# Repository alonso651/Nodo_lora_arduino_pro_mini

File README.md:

Nodo loRaWan para Arduino Pro Mini Atmega328p 3.3v
==================================================
Febrero de 2019 

Este programa fue desarrollado a partir del código ejemplo de la libreria LMiC 1.51 port to ESP8266 and Arduino [LMiC-v1.51](libraries/lmic-v1.51/README.md), 
publicada en http://things4u.github.io por M. Westenberg.

Esta libreria implementa la pila para una red LoRa.
Contiene la pila completa de LoRa y funciona en la plataforma Teensy, ESP8266 y en el Ardino Atmega328.

LMIC 1.5 port to ESP8266 and Arduino esta compuesta de dos bibliotecas existentes:

1. La biblioteca LMIC-1.5 de IBM, que fue portada a Arduino IDE por Thomas Telkamp y Matthijs Kooijman
2. La pequeña implementación para Arduino hecha por Gerben den Hartog para Ideetron.

Nodo LoRaWAN
------------
Este programa envia un paquete LoRaWAN válido con la lectura de sensores al servidor The Things Network (TTN).

Utiliza el método de autenticación ABP, tambien es posible utilizar el método de activación OTAA, 
aunque este no fue probado aún.

Se utilizó la Banda de frecuencias ISM US915 MHz, que cuenta con 72 canales, 
de los cuales solo utilizamos los 8 canales de la segunda sub banda (Sub Banda 1).

Sub banda 1 (903.9 - 905.3 MHz): 

	· Canal 0 - 903.9 MHz
	· Canal 1 - 904.1 MHz
	· Canal 2 - 904.3 MHz
	· Canal 3 - 904.5 MHz
	· Canal 4 - 904.7 MHz
	· Canal 5 - 904.9 MHz
	· Canal 6 - 905.1 MHz
	· Canal 7 - 905.3 MHz
Es posible utilizar los factores de esparcimiento SF (Spreading Factor) del 7 al 12, solo fue probado 
con el SF7.

Hardware
--------
	· Arduino Pro Mini Atmega328p 3,3V 8MHz
	· HopeRF RFM95w de 915MHz  

Conexiones
----------
	 _____________________________
	|   RFM95w   |Arduino Pro Mini|
	|____________|________________|
	|GND         |GND             |
	|3.3v        |VCC (3.3v)      |
	|MISO        |12              |
	|MOSI        |11              |
	|SCK         |13              |
	|NSS         |10              |
	|DIO0        |4               |
	|DIO1        |5               |
	|DIO2        |7               |
	|____________|________________|

Modificaciónes hechas a la libreria LMIC 1.5 port to ESP8266 and Arduino:
-------------------------------------------------------------------------
lmic.cpp: LMIC_disableChannel(u1_t channel) 

	//LMIC.channelMap[channel/4] &= ~(1<<(channel&0xF)); 
    LMIC.channelMap[channel/16] &= ~(1<<(channel&0xF));

TTGO Pro Mini_LORA 20180926 - T-DEER:
-------------------------------------

	· Es necesario conectar dos pines de la placa entre si (puente) D5 - IO1
	· La definicion de pines es diferente que en el Arduino Pro Mini (Descomentar en el código fuente 
	y comentar la definición de pines anterior)
	· Se lo programa como Arduino UNO (En Arduino IDE)

	.

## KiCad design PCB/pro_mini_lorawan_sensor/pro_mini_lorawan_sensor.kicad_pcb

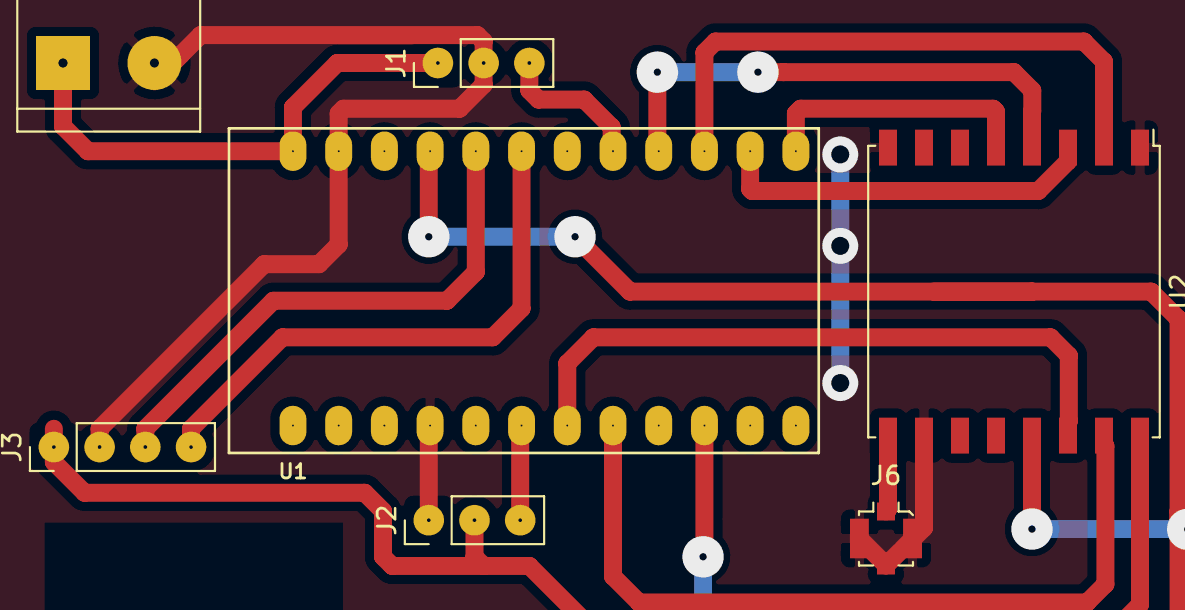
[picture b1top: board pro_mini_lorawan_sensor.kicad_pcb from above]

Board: 2 copper layers, 7 parts (0 on the bottom side), 15 nets.

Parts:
J1: Sensor de Humo; PinHeader_1x03_P2.54mm_Vertical
J2: Sensor de Llama; PinHeader_1x03_P2.54mm_Vertical
J3: BME280; PinHeader_1x04_P2.54mm_Vertical
J4: Entrada 5V; TerminalBlock_bornier-2_P5.08mm
J6: Conector Antena; U.FL_Molex_MCRF_73412-0110_Vertical
U1: pro_mini
U2: RFM95W; HOPERF_RFM9XW_SMD

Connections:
/3v3: J2.2, J3.1, U1.21, U2.13
/5V: J1.1, J4.1, U1.24
/A0: J1.3, U1.17
/ANT: J6.1, U2.9
/D3: J2.3, U1.6
/DIO0: U1.7, U2.14
/DIO1: U1.8, U2.15
/DIO2: U1.10, U2.16
/GND: J1.2, J2.1, J3.2, J4.2, J6.2, U1.4, U1.23, U2.1, U2.8, U2.10
/MISO: U1.15, U2.2
/MOSI: U1.14, U2.3
/NSS: U1.13, U2.5
/SCK: U1.16, U2.4
/SCL: J3.4, U1.19
/SDA: J3.3, U1.20

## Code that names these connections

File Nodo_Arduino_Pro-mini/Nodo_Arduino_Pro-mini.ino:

/*Nodo LoRa ABP Arduino Pro Mini 3v3 Atmega328p 8MHz

  Banda de frecuencia US915 MHz
  Sub Banda 1 (903.9 - 905.3) ---> Configuración del Gateway Single Channel ESP
  Canal 0 (de la sub banda 1) ---> Configuración del Gateway Single Channel ESP
  Canal en el que envia 903.9 MHz (canal 8 de 72)

  Radio HopeRF RFM95w (SX1276) 915MHz 

  Libreria: LMiC v1.5 *Modificada*
    Modificación: lmic.cpp LMIC_disableChannel(u1_t channel) 
      //LMIC.channelMap[channel/4] &= ~(1<<(channel&0xF)); 
      LMIC.channelMap[channel/16] &= ~(1<<(channel&0xF));

  Conexión de pines (Arduino Pro Mini):
   _____________________________
  |   RFM95w   |Arduino Pro Mini|
  |____________|________________|
  |GND         |GND             |
  |3.3v        |VCC (3.3v)      |
  |MISO        |12              |
  |MOSI        |11              |
  |SCK         |13              |
  |NSS         |10              |
  |DIO0        |4               |
  |DIO1        |5               |
  |DIO2        |7               |
  |____________|________________|

  Conexión de pines (TTGO Pro Mini_LORA - T-DEER):

    Puente entre los pines D5 y IO1 (Necesario para que envie mas de un paquete)
*/


//#define WAIT_SECS 120   //60 Segundos en Arduino Pro Mini
//#define WAIT_SECS 60  //60 Segundos en TTGO Pro Mini_LORA - T-DEER
#define WAIT_SECS 15  //15 Segundos en TTGO Pro Mini_LORA - T-DEER


#if defined(__AVR__)
#include <avr/pgmspace.h>
#include <Arduino.h>
#elif defined(ARDUINO_ARCH_ESP8266)
#include <ESP.h>
#elif defined(__MKL26Z64__)
#include <Arduino.h>
#else
#error Unknown architecture in aes.cpp
#endif

#include "lmic.h"
#include "hal/hal.h"
#include <SPI.h>

//---------------------------------------------------------
// Declaracion de variables
//---------------------------------------------------------

// Contador de tramas
int count=0;

// LoRaWAN Application identifier (AppEUI)
// No usado
static const u1_t APPEUI[8] PROGMEM = { 0x02, 0x00, 0x00, 0x00, 0x00, 0xEE, 0xFF, 0xC0 };

// LoRaWAN DevEUI
// No usado
static const u1_t DEVEUI[8] PROGMEM  = { 0x42, 0x42, 0x45, 0x67, 0x89, 0xAB, 0xCD, 0xEF };

// LoRaWAN NwkSKey, Network Session Key 
// Network Session Key The Things Network
unsigned char NwkSkey[16] =     { 0xE9, 0x01, 0xE2, 0x79, 0x10, 0x18, 0xF1, 0x40, 0xB7, 0xF7, 0xBA, 0x6D, 0x5C, 0x04, 0x01, 0xB7 };

// LoRaWAN AppSKey, Application Session Key
// Application Session Key para desencriptación de mensajes en The Things Network
unsigned char AppSkey[16] =   { 0x0E, 0xBE, 0x00, 0xE7, 0x66, 0x10, 0xE5, 0x3A, 0x19, 0x0B, 0xC6, 0x8C, 0x71, 0x1C, 0xAA, 0x22 };


#define msbf4_read(p)   (u4_t)((u4_t)(p)[0]<<24 | (u4_t)(p)[1]<<16 | (p)[2]<<8 | (p)[3])

// LoRaWAN end-device address (DevAddr)
unsigned char DevAddr[4] = { 0x26, 0x06, 0x2C, 0xE1 };


// ----------------------------------------------------------------------------
// APPLICATION CALLBACKS
// ----------------------------------------------------------------------------

// Desabilitar todos los canales, excepto el canal definido en el if de ForceTxSingleChannelDr()
// Setear el SF en LMIC_setDrTxpow() al final de esta función.
// Esto solo afecta a los mensajes enviados (uplinks). 

void forceTxSingleChannelDr() {
    for(int j=0; j<71; j++) { // US i<71 canales
        if(j != 8) {
            LMIC_disableChannel(j);
        }
    }
    // Set data rate (SF) and transmit power for uplink
    LMIC_setDrTxpow(DR_SF10, 14);
}

// provide application router ID (8 bytes, LSBF)
void os_getArtEui (u1_t* buf) {
    memcpy(buf, APPEUI, 8);
}

// provide device ID (8 bytes, LSBF)
void os_getDevEui (u1_t* buf) {
    memcpy(buf, DEVEUI, 8);
}

// provide device key (16 bytes)
void os_getDevKey (u1_t* buf) {
    memcpy(buf, NwkSkey, 16);
}

int debug=1;
uint8_t mydata[64];
static osjob_t sendjob;

// ----------------------------------------------------------------------------
// Pin mapping (Arduino Pro Mini)
// ----------------------------------------------------------------------------

// lmic_pinmap pins = {
//   .nss = 10,          // Conectado a D10 (Arduino Pro Mini)
//   .rxtx = 0,          // No conectar al RFM92/RFM95
//   .rst = 0,           // No conectar al RFM92/RFM95
//   .dio = {4, 5, 7},   // Especificación de pines DIO0, DIO1, DIO2 (RFM95)
//                       // Conectado a D4, D5, D7 (Arduino Pro Mini)
// };

// ----------------------------------------------------------------------------
// Pin mapping (TTGO Pro Mini_LORA 20180926 - T-DEER) 
// ----------------------------------------------------------------------------

lmic_pinmap pins = {
  .nss = 10,          // Conectado a D10 (TTGO Pro Mini_LORA)
  .rxtx = 0,          // No conectar al RFM92/RFM95
  .rst = 9,           // Conectado a D9 (TTGO Pro Mini_LORA)
  .dio = {2, 5, 0},   // Especificación de pines DIO0, DIO1, DIO2 (RFM95)
                      // Conectado a D2, D5, No Conectar (TTGO Pro Mini_LORA)
};

// ----------------------------------------------------------------------------
// Declaración de funciones
// ----------------------------------------------------------------------------

void onEvent (ev_t ev) {

    switch(ev) {
      // scheduled data sent (optionally data received)
      // note: this includes the receive window!
      case EV_TXCOMPLETE:
          // use this event to keep track of actual transmissions
          Serial.print("EV_TXCOMPLETE, tiempo: ");
          //Serial.print((millis() / 1000)/2); //Pro Mini
          Serial.print((millis() / 1000));
          Serial.println(" Segundos");
          if(LMIC.dataLen) { // Datos recibidos en la ventana de recepción (RX slot) luego del envio de datos (TX)
              Serial.println("Data Received");
          }
          break;
       default:
          break;
    }
}

void do_send(osjob_t* j){
    delay(1);                         // delay agregado para la comunicación serial
      Serial.print("Tiempo: ");
      //Serial.print((millis() / 1000)/2); //Pro Mini
      Serial.print((millis() / 1000));
      Serial.println(" Segundos");
      // Muestra el canal TX 
      Serial.print("Enviado. Canal: ");
      Serial.println(LMIC.txChnl);
      Serial.print("Opmode check: ");
      // Check if there is not a current TX/RX job running
    if (LMIC.opmode & (1 << 7)) {
      Serial.println("OP_TXRXPEND, not sending");
    } 
  else {
  
    strcpy((char *) mydata,"Arduino Pro Mini"); //Mensaje que se envia a TTN
    LMIC_setTxData2(1, mydata, strlen((char *)mydata), 0);
    }
    // Schedule a timed job to run at the given timestamp (absolute system time)
    os_setTimedCallback(j, os_getTime()+sec2osticks(WAIT_SECS), do_send);
         
}

// ----------------------------------------------------------------------------
// SETUP
// ----------------------------------------------------------------------------
void setup() {
  Serial.begin(115200);

  // Inicializacion de LMiC
  os_init();
  // Definición de la banda de frecuencia a utilizar (No se si cumple alguna función esto aquí)
  #if defined(CFG_us915)
  LMIC.freq = 903900000;
  #endif
  // Resetea el estado de la MAC. Sesión o datos pendientes de envio serán descartados
  LMIC_reset();
  // Establece la sesión con los parametros suministrados en la sección "Declaración de Variables"
  LMIC_setSession (0x1, msbf4_read(DevAddr), (uint8_t*)NwkSkey, (uint8_t*)AppSkey);
  // Desabilita la adaptación de SF (configuración para nodos móviles)
  LMIC_setAdrMode(0);
  // Disabilita link check validation
  LMIC_setLinkCheckMode(0);
  // Desabilita beacon tracking
  LMIC_disableTracking ();
  // Desabilita la recepcion periodica de datos (configuración para dispositivos LoRaWAN Clase A)
  LMIC_stopPingable();
  // Establece el canal, SF y potencia del transmisor para el envio de datos
  forceTxSingleChannelDr(); //reemplazar valores en la definición de la función forceTxSingleChannelDr() en la sección "Declaración de funciones"
  
#if defined(__AVR__)
  Serial.println("AVR arch");
#elif defined(ARDUINO_ARCH_ESP8266)
  Serial.println("ESP arch");
#elif defined(__MKL26Z64__)
  Serial.println("Teensy arch");
#else
  Serial.println("WARNING. Unknown Arch");
#endif

}

// ----------------------------------------------------------------------------
// LOOP
// ----------------------------------------------------------------------------
void loop() {

  do_send(&sendjob);
  while(1) {
    os_runloop_once(); 
    delay(100);
  }
}

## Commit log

2019-02-13 Creacion del repositorio
    Primer commit
2019-02-13 readme
    Readme
2019-02-13 Nodo LoRaWAN
    Nodo LoRaWAN Arduino Pro Mini 3v3
2019-02-13 Librerias
    Librerias
2019-03-05 Nodo LoRaWAN
2019-03-05 Readme
2019-03-05 Esquema de conexiones de TTGO Pro Mini_LORA T-DEER
2019-03-05 TTGO Pro Mini_LORA T-DEER
2019-03-05 Nodo Arduino Pro Mini
2019-03-15 ATmega328
2019-04-02 ATmega 168
    Imagen del pinout
